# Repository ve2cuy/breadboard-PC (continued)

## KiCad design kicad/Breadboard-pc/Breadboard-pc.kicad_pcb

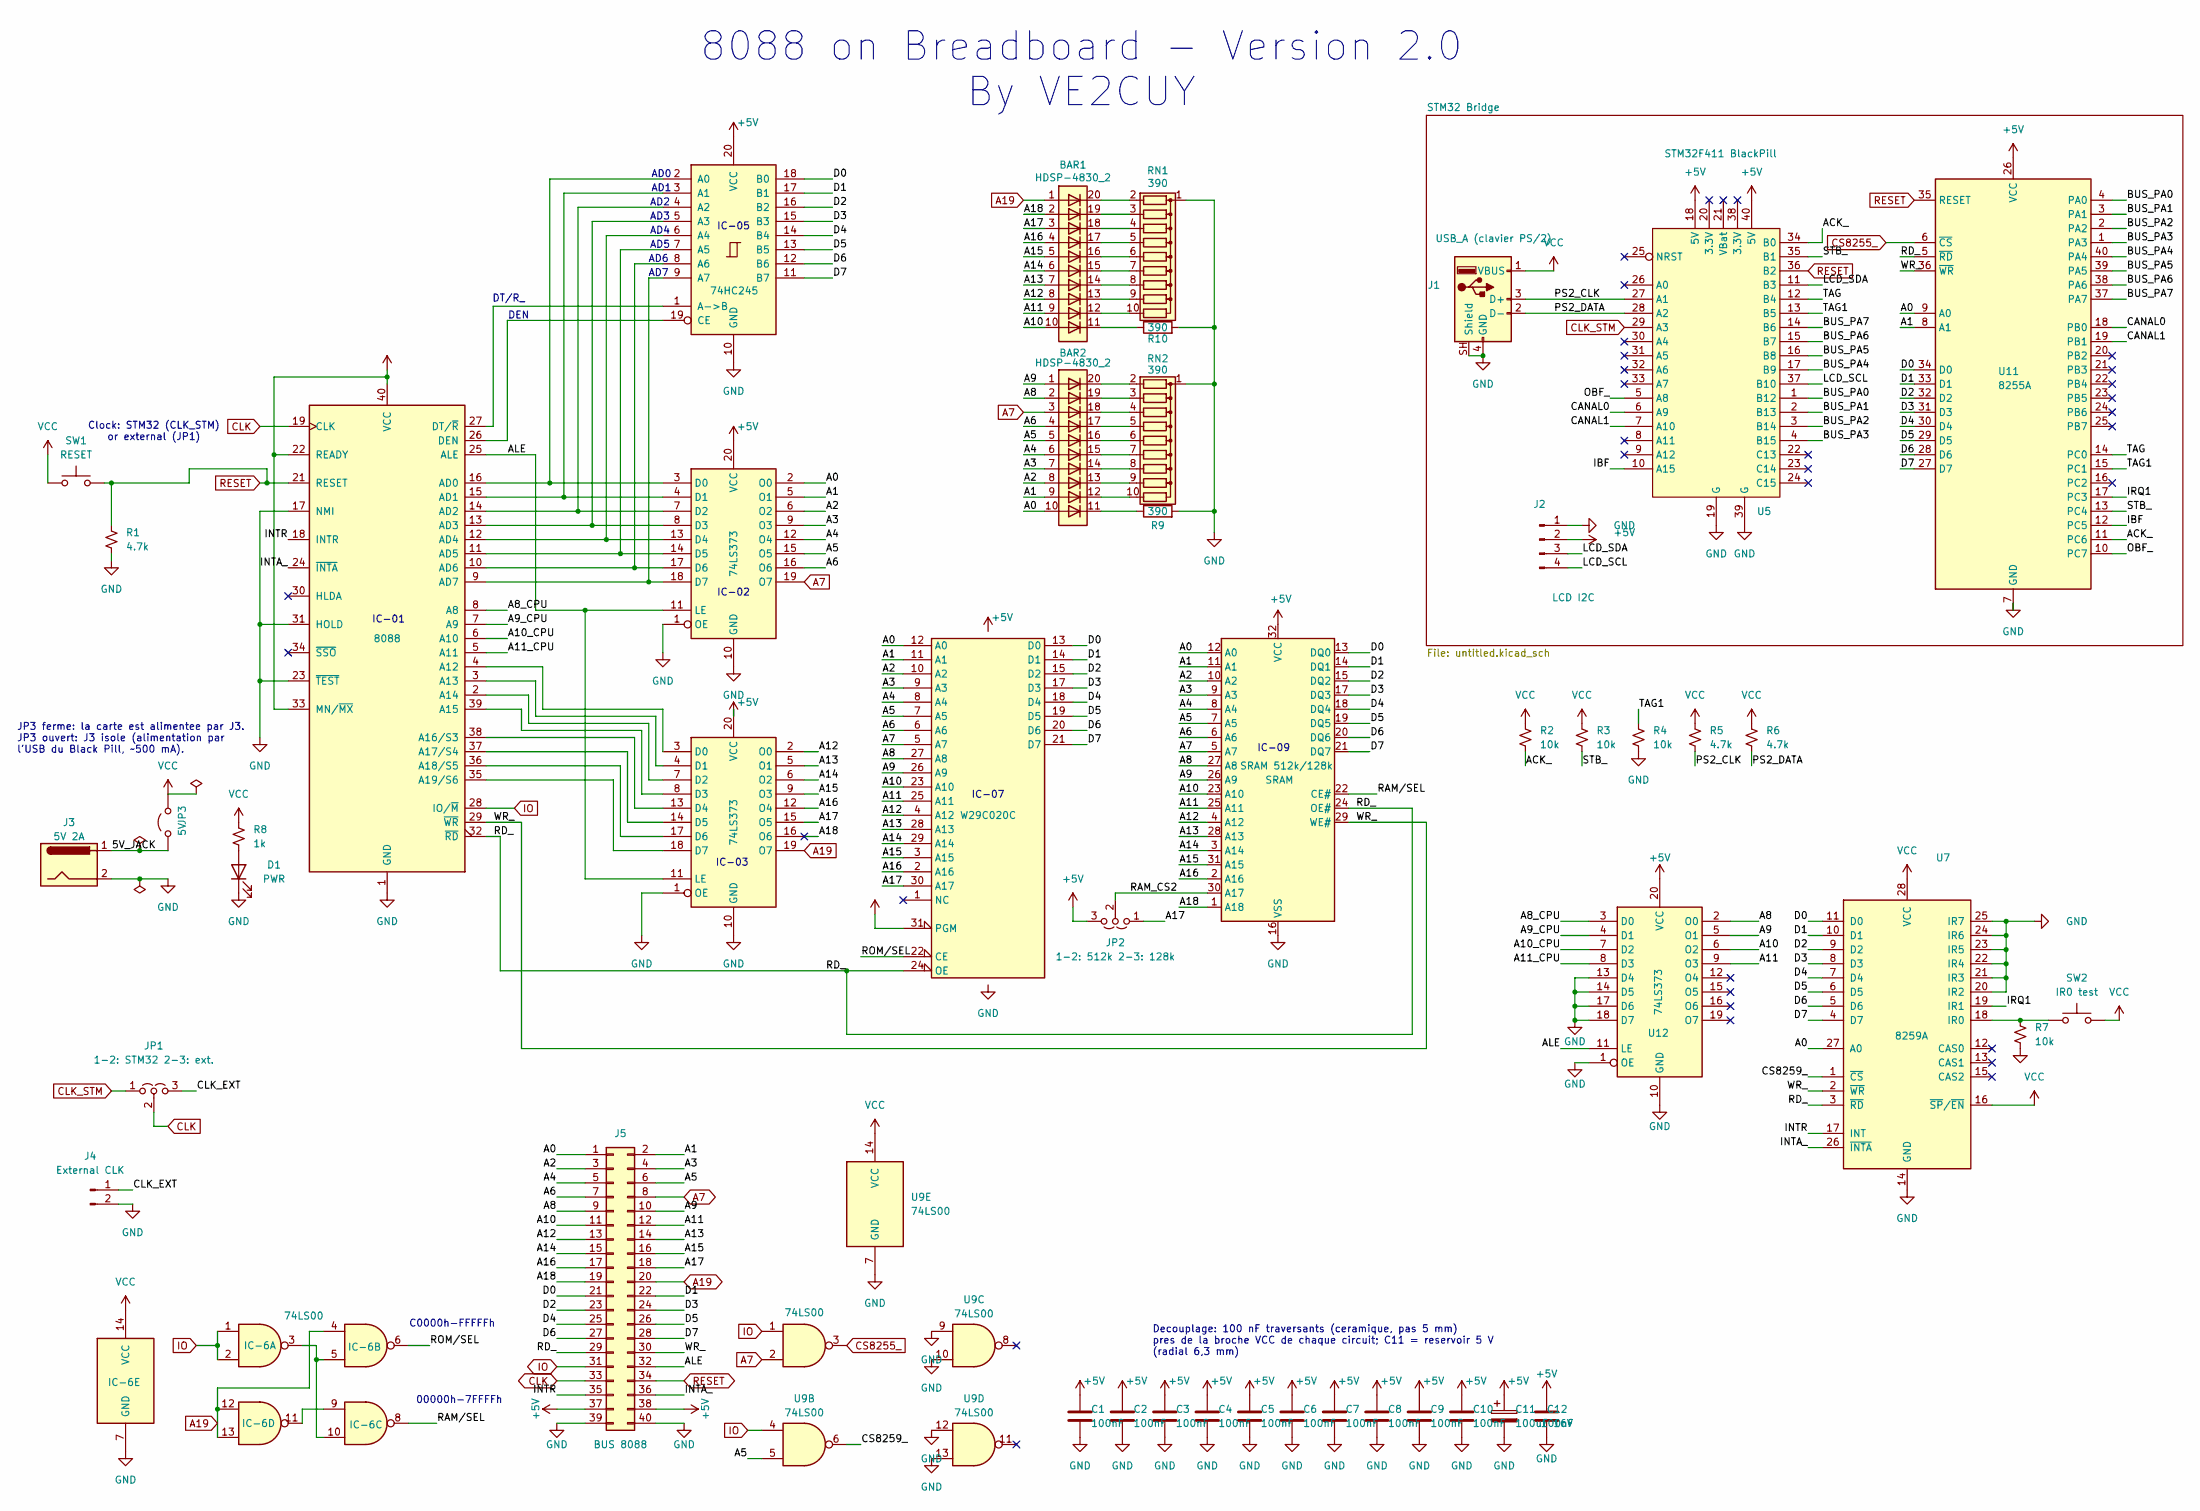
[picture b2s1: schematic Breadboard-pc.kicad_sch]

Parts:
BAR1, BAR2: HDSP-4830_2; HDSP-4830
C1, C2, C3, C4, C5, C6, C7, C8, C9, C10, C12: 100nF; C_Disc_D5.0mm_W2.5mm_P5.00mm
C11: 100uF 16V; CP_Radial_D6.3mm_P2.50mm
D1: PWR; LED_D3.0mm
IC-6: 74LS00; DIP-14_W7.62mm
J1: USB_A (clavier PS/2); USB_A_Molex_67643_Horizontal
J2: LCD I2C; PinHeader_1x04_P2.54mm_Vertical
J3: 5V 2A; BarrelJack_Horizontal
J4: External CLK; PinHeader_1x02_P2.54mm_Vertical
J5: BUS 8088; PinHeader_2x20_P2.54mm_Vertical
JP1: 1-2: STM32 2-3: ext.; PinHeader_1x03_P2.54mm_Vertical
JP2: 1-2: 512k 2-3: 128k; PinHeader_1x03_P2.54mm_Vertical
JP3: 5V; PinHeader_1x02_P2.54mm_Vertical
R1, R5, R6: 4.7k; R_Axial_DIN0207_L6.3mm_D2.5mm_P7.62mm_Horizontal
R2, R3, R4, R7: 10k; R_Axial_DIN0207_L6.3mm_D2.5mm_P7.62mm_Horizontal
R8: 1k; R_Axial_DIN0207_L6.3mm_D2.5mm_P7.62mm_Horizontal
R9, R10: 390; R_Axial_DIN0207_L6.3mm_D2.5mm_P7.62mm_Horizontal
RN1, RN2: 390; R_Array_SIP10
SW1: RESET; SW_PUSH_6mm
SW2: IR0 test; SW_PUSH_6mm
U1: 8088; DIP-40_W15.24mm
U2, U3, U12: 74LS373; DIP-20_W7.62mm
U4: W29C020C; DIP_Socket-32_W11.9mm_W12.7mm_W15.24mm_W17.78mm_W18.5mm_3M_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
U5: STM32F411 BlackPill; STM32F411_Black_Pill
U6: 74HC245; DIP-20_W7.62mm
U7: 8259A; DIP-28_W15.24mm
U8: SRAM; DIP-32_W15.24mm
U9: 74LS00; DIP-14_W7.62mm
U11: 8255A; DIP-40_W15.24mm

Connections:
/5V_JACK: J3.1, JP3.1 (A)
/A0: BAR2.10 (A), J5.1, U2.2 (O0), U4.12 (A0), U7.27 (A0), U8.12 (A0), U11.9 (A0)
/A1: BAR2.9 (A), J5.2, U2.5 (O1), U4.11 (A1), U8.11 (A1), U11.8 (A1)
/A2: BAR2.8 (A), J5.3, U2.6 (O2), U4.10 (A2), U8.10 (A2)
/A3: BAR2.7 (A), J5.4, U2.9 (O3), U4.9 (A3), U8.9 (A3)
/A4: BAR2.6 (A), J5.5, U2.12 (O4), U4.8 (A4), U8.8 (A4)
/A5: BAR2.5 (A), J5.6, U2.15 (O5), U4.7 (A5), U8.7 (A5), U9.5
/A6: BAR2.4 (A), J5.7, U2.16 (O6), U4.6 (A6), U8.6 (A6)
/A8: BAR2.2 (A), J5.9, U4.27 (A8), U8.27 (A8), U12.2 (O0)
/A8_CPU: U1.8 (A8), U12.3 (D0)
/A9: BAR2.1 (A), J5.10, U4.26 (A9), U8.26 (A9), U12.5 (O1)
/A9_CPU: U1.7 (A9), U12.4 (D1)
/A10: BAR1.10 (A), J5.11, U4.23 (A10), U8.23 (A10), U12.6 (O2)
/A10_CPU: U1.6 (A10), U12.7 (D2)
/A11: BAR1.9 (A), J5.12, U4.25 (A11), U8.25 (A11), U12.9 (O3)
/A11_CPU: U1.5 (A11), U12.8 (D3)
/A12: BAR1.8 (A), J5.13, U3.2 (O0), U4.4 (A12), U8.4 (A12)
/A13: BAR1.7 (A), J5.14, U3.5 (O1), U4.28 (A13), U8.28 (A13)
/A14: BAR1.6 (A), J5.15, U3.6 (O2), U4.29 (A14), U8.3 (A14)
/A15: BAR1.5 (A), J5.16, U3.9 (O3), U4.3 (A15), U8.31 (A15)
/A16: BAR1.4 (A), J5.17, U3.12 (O4), U4.2 (A16), U8.2 (A16)
/A17: BAR1.3 (A), J5.18, JP2.1 (A), U3.15 (O5), U4.30 (A17)
/A18: BAR1.2 (A), J5.19, U3.16 (O6), U8.1 (NC)
/ACK_: R2.2, U5.34 (B0), U11.11 (PC6)
/ALE: J5.32, U1.25 (ALE), U2.11 (LE), U3.11 (LE), U12.11 (LE)
/BUS_PA0: U5.1 (B12), U11.4 (PA0)
/BUS_PA1: U5.2 (B13), U11.3 (PA1)
/BUS_PA2: U5.3 (B14), U11.2 (PA2)
/BUS_PA3: U5.4 (B15), U11.1 (PA3)
/BUS_PA4: U5.17 (B9), U11.40 (PA4)
/BUS_PA5: U5.16 (B8), U11.39 (PA5)
/BUS_PA6: U5.15 (B7), U11.38 (PA6)
/BUS_PA7: U5.14 (B6), U11.37 (PA7)
/CANAL0: U5.6 (A9), U11.18 (PB0)
/CANAL1: U5.7 (A10), U11.19 (PB1)
/CLK_EXT: J4.1, JP1.3 (B)
/CS8259_: U7.1 (~CS), U9.6
/D0: J5.21, U4.13 (D0), U6.18 (B0), U7.11 (D0), U8.13 (DQ0), U11.34 (D0)
/D1: J5.22, U4.14 (D1), U6.17 (B1), U7.10 (D1), U8.14 (DQ1), U11.33 (D1)
/D2: J5.23, U4.15 (D2), U6.16 (B2), U7.9 (D2), U8.15 (DQ2), U11.32 (D2)
/D3: J5.24, U4.17 (D3), U6.15 (B3), U7.8 (D3), U8.17 (DQ3), U11.31 (D3)
/D4: J5.25, U4.18 (D4), U6.14 (B4), U7.7 (D4), U8.18 (DQ4), U11.30 (D4)
/D5: J5.26, U4.19 (D5), U6.13 (B5), U7.6 (D5), U8.19 (DQ5), U11.29 (D5)
/D6: J5.27, U4.20 (D6), U6.12 (B6), U7.5 (D6), U8.20 (DQ6), U11.28 (D6)
/D7: J5.28, U4.21 (D7), U6.11 (B7), U7.4 (D7), U8.21 (DQ7), U11.27 (D7)
/IBF: U5.10 (A15), U11.12 (PC5)
/INTA_: J5.36, U1.24 (~INTA), U7.26 (~INTA)
/INTR: J5.35, U1.18 (INTR), U7.17 (INT)
/IRQ1: U7.19 (IR1), U11.17 (PC3)
/LCD_SCL: J2.4, U5.37 (B10)
/LCD_SDA: J2.3, U5.11 (B3)
/OBF_: U5.5 (A8), U11.10 (PC7)
/PS2_CLK: J1.3 (D+), R5.2, U5.27 (A1)
/PS2_DATA: J1.2 (D-), R6.2, U5.28 (A2)
/RAM_CS2: JP2.2 (C), U8.30 (CS2)
/RAM/SEL: IC-6.8, U8.22 (CE#)
/RD_: J5.29, U1.32 (~RD), U4.24 (OE), U7.3 (~RD), U8.24 (OE#), U11.5 (~RD)
/ROM/SEL: IC-6.6, U4.22 (CE)
/STB_: R3.2, U5.35 (B1), U11.13 (PC4)
/TAG: U5.12 (B4), U11.14 (PC0)
/TAG1: R4.1, U5.13 (B5), U11.15 (PC1)
/WR_: J5.30, U1.29 (~WR), U7.2 (~WR), U8.29 (WE#), U11.36 (~WR)
A7: BAR2.3 (A), J5.8, U2.19 (O7), U4.5 (A7), U8.5 (A7), U9.2
A19: BAR1.1 (A), IC-6.4, IC-6.12, IC-6.13, J5.20, U3.19 (O7)
CLK: J5.33, JP1.2 (C), U1.19 (CLK)
CLK_STM: JP1.1 (A), U5.29 (A3)
CS8255_: U9.3, U11.6 (~CS)
GND: C1.2, C2.2, C3.2, C4.2, C5.2, C6.2, C7.2, C8.2, C9.2, C10.2, C11.2, C12.2, D1.1 (K), IC-6.7 (GND), J1.4 (GND), J1.SH (Shield), J2.1, J3.2, J4.2, J5.39, J5.40, R1.2, R4.2, R7.2, R9.2, R10.2, RN1.1 (common), RN2.1 (common), U1.1 (GND), U1.17 (NMI), U1.20 (GND), U1.23 (~TEST), U1.31 (HOLD), U2.1 (OE), U2.10 (GND), U3.1 (OE), U3.10 (GND), U4.16 (GND), U5.19 (G), U5.39 (G), U6.10 (GND), U7.14 (GND), U7.20 (IR2), U7.21 (IR3), U7.22 (IR4), U7.23 (IR5), U7.24 (IR6), U7.25 (IR7), U8.16 (VSS), U9.7 (GND), U9.9, U9.10, U9.12, U9.13, U11.7 (GND), U12.1 (OE), U12.10 (GND), U12.13 (D4), U12.14 (D5), U12.17 (D6), U12.18 (D7)
IO: IC-6.1, IC-6.2, J5.31, U1.28 (IO/~M), U9.1, U9.4
unnamed: BAR1.11 (K), R10.1
unnamed: BAR2.11 (K), R9.1
unnamed: D1.2 (A), R8.2
unnamed: IC-6.3, IC-6.5, IC-6.10
unnamed: IC-6.9, IC-6.11
unnamed: BAR1.20 (K), RN1.2 (R1)
unnamed: BAR1.19 (K), RN1.3 (R2)
unnamed: BAR1.18 (K), RN1.4 (R3)
unnamed: BAR1.17 (K), RN1.5 (R4)
unnamed: BAR1.16 (K), RN1.6 (R5)
unnamed: BAR1.15 (K), RN1.7 (R6)
unnamed: BAR1.14 (K), RN1.8 (R7)
unnamed: BAR1.13 (K), RN1.9 (R8)
unnamed: BAR1.12 (K), RN1.10 (R9)
unnamed: BAR2.20 (K), RN2.2 (R1)
unnamed: BAR2.19 (K), RN2.3 (R2)
unnamed: BAR2.18 (K), RN2.4 (R3)
unnamed: BAR2.17 (K), RN2.5 (R4)
unnamed: BAR2.16 (K), RN2.6 (R5)
unnamed: BAR2.15 (K), RN2.7 (R6)
unnamed: BAR2.14 (K), RN2.8 (R7)
unnamed: BAR2.13 (K), RN2.9 (R8)
unnamed: BAR2.12 (K), RN2.10 (R9)
unnamed: U1.4 (A12), U3.3 (D0)
unnamed: U1.3 (A13), U3.4 (D1)
unnamed: U1.2 (A14), U3.7 (D2)
unnamed: U1.39 (A15), U3.8 (D3)
unnamed: U1.38 (A16/S3), U3.13 (D4)
unnamed: U1.37 (A17/S4), U3.14 (D5)
unnamed: U1.36 (A18/S5), U3.17 (D6)
unnamed: U1.35 (A19/S6), U3.18 (D7)
unnamed: U1.16 (AD0), U2.3 (D0), U6.2 (A0)
unnamed: U1.15 (AD1), U2.4 (D1), U6.3 (A1)
unnamed: U1.14 (AD2), U2.7 (D2), U6.4 (A2)
unnamed: U1.13 (AD3), U2.8 (D3), U6.5 (A3)
unnamed: U1.12 (AD4), U2.13 (D4), U6.6 (A4)
unnamed: U1.11 (AD5), U2.14 (D5), U6.7 (A5)
unnamed: U1.10 (AD6), U2.17 (D6), U6.8 (A6)
unnamed: U1.9 (AD7), U2.18 (D7), U6.9 (A7)
unnamed: U1.26 (DEN), U6.19 (CE)
unnamed: U1.27 (DT/~R), U6.1 (A->B)
unnamed: R7.1, SW2.1, U7.18 (IR0)
RESET: J5.34, R1.1, SW1.2, U1.21 (RESET), U5.36 (B2), U11.35 (RESET)

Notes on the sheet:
IC-07
Decouplage: 100 nF traversants (ceramique, pas 5 mm) pres de la broche VCC de chaque circuit; C11 = reservoir 5 V (radial 6,3 mm)
C0000h-FFFFFh
00000h-7FFFFh
IC-05
AD2
DEN
IC-01
AD5
IC-03
AD4
AD0
DT/R_
IC-09
AD3
JP3 ferme: la carte est alimentee par J3. JP3 ouvert: J3 isole (alimentation par l'USB du Black Pill, ~500 mA).
IC-02
AD6
AD1
Clock: STM32 (CLK_STM) or external (JP1)
AD7
8088 on Breadboard - Version 2.0 By VE2CUY

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
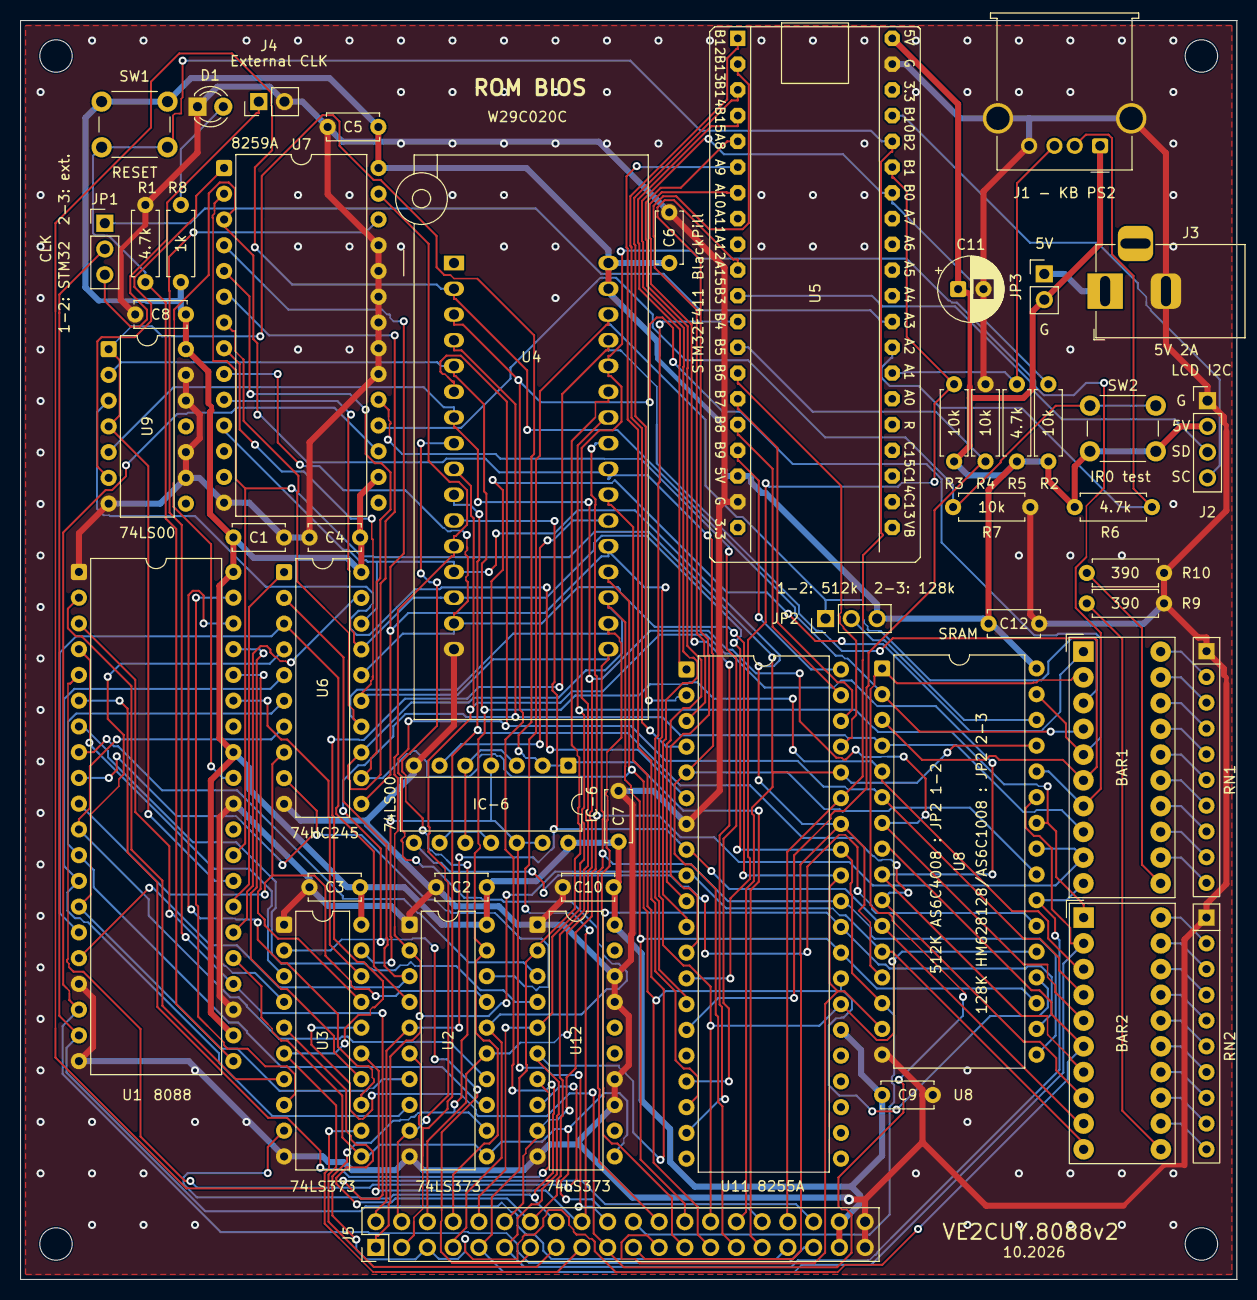
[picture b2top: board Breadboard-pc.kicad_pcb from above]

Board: 2 copper layers, 120.0 x 124.2 mm, 53 parts (0 on the bottom side), 113 nets.

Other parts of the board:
H1, H2, H3, H4: M3; MountingHole_3.2mm_M3

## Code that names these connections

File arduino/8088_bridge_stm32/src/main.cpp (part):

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//   - UART          : port serie virtuel USB (USB natif, "Serial") <-> 8088;
//   - LCD 20x4 I2C  : possede le bus I2C et le protocole PCF8574/HD44780.
//
// 8088 -> pont : le 8088 pose le CANAL sur le Port B (PB0/PB1 du 8255) puis
//     ecrit le Port A; OBF# passe a 0. On lit le canal, on abaisse ACK#, on lit
//     l'octet, on relache ACK#. canal 0 = octet UART, 1 = commande LCD, 2 =
//     donnee LCD.
// pont -> 8088 : on pose l'etiquette TAG (PC0: 0 = scan code, 1 = octet UART
//     recu; PC1 = 1: REPONSE a une commande), l'octet sur le bus, et on pulse
//     STB#; INTR du 8255 (sur IR1 du 8259) interrompt le 8088.
// canal 3 = COMMANDES pour le pont (voir Solution-01/lib/bridge.asm):
//     00h PING (reponse B1h, 3, capacites)   01h LIRE l'heure (reponse: 8 octets)
//     02h + 7 octets REGLER l'heure (annee 2 octets, mois, jour, h, min, s).
//     03h VERSION du firmware (PAS le "3" de PING ci-dessus, qui est le numero
//     de VERSION DU PROTOCOLE - sans rapport) -> 2 octets (majeure, mineure).
//     Necessite TAG1 (PB5) relie a PC1 du 8255 (tire a 0 par 10 kohm).
//     10h-19h = DISQUE: fichiers FAT (racine, noms 8.3) sur la flash SPI (W25Q64, 8 Mo) de la carte
//     (PA4 = CS, SPI1 PA5/PA6/PA7): statut, formater, ouvrir, lire, ecrire, fermer,
//     repertoire (debut / suivant), supprimer, espace libre. Voir lib/bridge.asm.
//     2Ch + 1 octet (action) = HORLOGE du 8088 (PA3, PWM materiel, voir clockExec ci-dessous):
//     0 lire, 1 +0,1 MHz, 2 -0,1 MHz, 3 +1 MHz, 4 -1 MHz, 5 -> 4,77 MHz, 6 -> 8 MHz
//     -> reponse 4 octets = Hz resultant.
//     Horloge de 1 Hz a 10 MHz (pont 2.0) par raccourcis traites ICI, sans le 8088 (a 1 Hz il
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//     l'appelle par INT 1Ah AH=E0h). Arret au reset du 8088.
//
// CABLAGE (voir le tableau du README.md)
//   D0-D3 <-> PB12-PB15 et D4-D7 <-> PB6-PB9  <->  8255 PA0-PA7 (bus de donnees)
//   PB0 -> ACK# (PC6)   PB1 -> STB# (PC4)   PA8 <- OBF# (PC7)   PB4 -> TAG (PC0)
//   PA9 <- canal bit 0 (8255 PB0)   PA10 <- canal bit 1 (8255 PB1)
//   PA15 <- IBF (PC5, facultatif)   PB5 -> TAG1 (PC1)
//   PA3 -> CLK du 8088 (broche 19, PWM materiel TIM2 CH4 - remplace le fil depuis l'Arduino UNO
//   R4 de projets/Clock-8088/; PA3 servait a TAG2/PC2, jamais cablee sur ce montage - libre)
//   PA1 <- CLK PS/2   PA2 <- DATA PS/2   PB10 = SCL, PB3 = SDA (LCD I2C2)
//   PA11/PA12 = USB, PA13/PA14 = SWD, PC13 = LED, PA4-PA7 = flash SPI (reservees),
//   PB2 -> RESET du 8088 (broche 21, actif HAUT; 4,7 kohm (R1) vers la masse sur le montage, bouton vers +5 V):
//   poussee HAUT pour un reset (demarrage du pont, Ctrl-Alt-Suppr au PS/2, Ctrl-\ au terminal), sinon
//   ENTREE (ne gene pas le bouton, jamais forcee BAS). PB2 = BOOT1: au repos la ligne est BASSE (4,7 kohm),
//   le mode DFU (BOOT0 = 1, BOOT1 = 0) reste donc utilisable.   PA0 = bouton K1 de la carte
// Selon la fiche technique du STM32F411 (DS10314 Rev 8, tableau 8), TOUTES ces
// broches sont tolerantes 5 V (FT) SAUF PA0 et PB5 (TC, 3,3 V): PB5 n'est donc
// utilisee qu'en SORTIE (TAG1). Ne jamais y relier une sortie 5 V.
// ============================================================================
#include <Wire.h>
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
// ---- reglages -------------------------------------------------------------
#define LCD_ADDR    0x27     // 0x3F pour un PCF8574A
// IBF (PC5 du 8255) cable sur PA15 ? 1 = oui: on n'envoie un octet que si le 8088 a lu le
// precedent (aucun octet ecrase); 0 = non cable. Non cable, PA15 est tiree a 0 (= libre).
#define USE_IBF     1
// Espace MINIMAL entre deux octets pont -> 8088, en plus de IBF. Le 8088 met ~ 0,5 ms
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#define ACK_BIT   0                  // GPIOB, sortie drain ouvert (10 kohm vers +5 V)
#define STB_BIT   1                  // GPIOB, sortie drain ouvert (10 kohm vers +5 V)
#define TAG_BIT   4                  // GPIOB, sortie
#define TAG1_BIT  5                  // GPIOB, sortie SEULEMENT (PB5 n'est pas tolerante 5 V)
#define OBF_BIT   8                  // GPIOA, entree
#define CH0_BIT   9                  // GPIOA, entrees (canal = Port B du 8255)
#define CH1_BIT   10
#define IBF_BIT   15                 // GPIOA, entree (facultatif)
#define PS2_CLK_BIT  1               // GPIOA, interruption EXTI1
#define PS2_DATA_BIT 2               // GPIOA
const uint32_t PIN_ACK = PB0, PIN_STB = PB1, PIN_TAG = PB4;
const uint32_t PIN_OBF = PA8, PIN_CH0 = PA9, PIN_CH1 = PA10, PIN_IBF = PA15;
const uint32_t PIN_TAG1 = PB5;                         // PC1 (etiquette etendue, futur)
const uint32_t PIN_PS2_CLK = PA1, PIN_PS2_DATA = PA2;
const uint32_t PIN_SCL = PB10, PIN_SDA = PB3;          // I2C2 (AF4 / AF9)
const uint32_t PIN_CLK8088 = PA3;                      // TIM2 CH4: horloge du 8088 (broche CLK, 19) -
                                                         // remplace le fil depuis l'Arduino UNO R4 (projets/Clock-8088)
                                                         // - PA3 servait a TAG2/PC2, jamais cablee sur ce montage

// Bus de donnees sur GPIOB, en deux quartets: D0-D3 = PB12-PB15, D4-D7 = PB6-PB9
#define BUS_ODR_MASK   ((0xFUL << 12) | (0xFUL << 6))
#define BUS_MODER_MASK 0xFF0FF000UL  // 2 bits par broche: PB12-15 (bits 24-31) et PB6-9 (bits 12-19)
#define BUS_MODER_OUT  0x55055000UL  // 01 = sortie
// Sur le montage, les broches PA4-PA7 du 8255 arrivent dans l'ORDRE INVERSE
// (constate: espace 0x20 recu 0x40, 'p' 0x70 recu 0xE0): le quartet haut est
// inverse (D4<->D7, D5<->D6), comme sur l'UNO. 1 = corrige en logiciel, 0 = bus
// cable dans l'ordre (D0-D7 <-> PA0-PA7).
#define BUS_HIGH_NIBBLE_REVERSED 1

// ---- canaux 8088 -> pont (Port B du 8255) ---------------------------------
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}

// ============================================================================
// Bus Port A du 8255 = PB12-PB15 (D0-D3) + PB6-PB9 (D4-D7) (MODER/BSRR/IDR)
// ============================================================================
static inline void busRelease() {          // haute impedance, sans pull
  GPIOB->MODER &= ~BUS_MODER_MASK;         // 00 = entree
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  stbHigh();                               // front montant: le 8255 verrouille
  delayMicroseconds(2);
#if DEBUG_FS
  dbgIbfAfter = (uint8_t)((GPIOA->IDR >> IBF_BIT) & 1);   // IBF doit valoir 1 (octet non lu)
#endif
  busRelease();
}
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}

// ============================================================================
// Horloge du 8088 (PA3 = TIM2 CH4, PWM materiel, duty cycle fixe 1/3 - voir
// projets/Clock-8088/src/main.cpp, meme principe mais sur l'Arduino UNO R4 separe
// d'origine: ici, l'horloge est generee par CE MEME pont, plus besoin de 2e carte).
// clockSetup() DOIT etre appelee EN PREMIER dans setup() (avant SPI/USB/RTC, qui
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
// ============================================================================
// Disque: systeme de fichiers FAT sur la flash SPI (W25Q64, 8 Mo) de la carte.
// Le STM32F411 n'a pas de QUADSPI: la flash s'utilise en SPI simple (SPI1: PA4 = CS,
// PA5 = SCK, PA6 = MISO, PA7 = MOSI). Fichiers a la racine, noms 8.3.
// ============================================================================
static Adafruit_FlashTransport_SPI flashTransport(PA4, SPI);
static Adafruit_SPIFlash flash(&flashTransport);
static FatVolume fatfs;
static bool flashOk = false, fsOk = false;
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}

// ============================================================================
// RESET materiel du 8088 (PB2 -> broche 21, RESET actif HAUT)
// Le montage tire RESET a la masse (4,7 kohm, R1) et son bouton le porte a +5 V: PB2 (tolerante 5 V) n'est
// donc JAMAIS forcee BAS - soit sortie HAUTE (reset en cours), soit ENTREE sans pull (le bouton marche).
// Demandes: demarrage du pont (setup: le 8088 reste en reset, horloge deja en marche, jusqu'a ce que le
// pont soit pret), Ctrl-Alt-Suppr au clavier PS/2 (kbdTrack, dans ps2Isr: detecte meme si le 8088 est
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#define RESET8088_BIT      2               // GPIOB
#define RESET8088_PULSE_MS 10UL            // >> 4 cycles d'horloge exiges par le 8088
#define RESET_UART_KEY     0x1C            // Ctrl-\ (terminal)
#define STUCK_MS           500UL           // IBF = 1 depuis ce delai: le 8088 ne lit plus (fige)
static volatile bool resetRequest = false;

static void reset8088Hold() {              // sortie HAUTE (ODR avant MODER: aucune impulsion basse)
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  // ACK#/STB#: DRAIN OUVERT. Le niveau haut est fourni par les 10 kohm vers +5 V
  // (vrai niveau 5 V pour le 8255, et lignes tenues hautes pendant un reset du
  // STM32). Pull-up interne en secours (3,3 V, suffisant pour l'entree TTL du 8255).
  pinMode(PIN_ACK, OUTPUT_OPEN_DRAIN);  ackHigh();  pullUp(GPIOB, ACK_BIT);
  pinMode(PIN_STB, OUTPUT_OPEN_DRAIN);  stbHigh();  pullUp(GPIOB, STB_BIT);
  pinMode(PIN_TAG, OUTPUT);   digitalWrite(PIN_TAG, LOW);
  pinMode(PIN_TAG1, OUTPUT);  digitalWrite(PIN_TAG1, LOW);   // PC1 (inutilise pour l'instant)
  pinMode(PIN_OBF, INPUT_PULLUP);          // 8255 absent/hors tension = "rien"
  pinMode(PIN_CH0, INPUT);
  pinMode(PIN_CH1, INPUT);
  pinMode(PIN_IBF, INPUT_PULLDOWN);        // non cable = "libre"

  // Bus (PB6-PB9, PB12-PB15): entrees, sans pull, sorties push-pull rapides.
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
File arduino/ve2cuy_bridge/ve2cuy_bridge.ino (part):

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// Le 8088 ne voit qu'UN bus de 8 bits: le Port A du 8255 en MODE 2, avec la
// poignee de main materielle du 8255 (voir Directives.md, hardware.inc):
//
//   8088 -> Arduino : le 8088 pose le CANAL sur le Port B (PB0/PB1) puis ecrit
//       le Port A; OBF# (PC7) passe a 0. On lit le canal, on abaisse ACK#
//       (PC6): le 8255 pilote alors le bus, on lit l'octet, on relache ACK#.
//       canal 0 = octet UART a emettre, 1 = commande LCD, 2 = donnee LCD.
//   Arduino -> 8088 : on pose l'etiquette (PC0: 0 = scan code, 1 = octet UART
//       recu), on pose l'octet sur le bus et on pulse STB# (PC4); INTR du 8255
//       (cable sur IR1 du 8259) interrompt le 8088.
//
// CABLAGE (18 broches, aucun circuit integre supplementaire)
//   D2  <- CLK  clavier PS/2 (interruption INT0)
//   D3  <- DATA clavier PS/2
//   D4  -> ACK#  8255 PC6        (repos: HAUT)   + pull-up 10k vers +5V conseille
//   D5  -> STB#  8255 PC4        (repos: HAUT)   + pull-up 10k vers +5V conseille
//   D6  <- OBF#  8255 PC7
//   D7  -> TAG   8255 PC0
//   D8  <- CH0   8255 PB0
//   D9  <- CH1   8255 PB1
//   D10 D11 D12 D13 A3 A2 A1 A0  <->  8255 PA0 PA1 PA2 PA3 PA4 PA5 PA6 PA7
//   (soit D10-D13 = PA0-PA3, A3=PA4, A2=PA5, A1=PA6, A0=PA7 - voir BUS[])
//   A4 (SDA), A5 (SCL) -> module LCD I2C (PCF8574, adresse 0x27 ou 0x3F)
//   INTR du 8255 (PC3) -> IR1 du 8259 (plus aucune sortie IR sur l'Arduino)
//   D0/D1 : reserves a l'USB (UART vers le PC) - ne rien y brancher.
//   Masse commune Arduino / breadboard 8088.
//
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#define DEBUG_PS2   0        // 1 = trace PS/2 sur le terminal (Serial), voir dbg*()

// ---- broches --------------------------------------------------------------
const uint8_t PIN_PS2_CLK  = 2;   // = PD2 (INT0) - ps2Isr lit PIND directement: garder CLK/DATA sur PD0-PD7
const uint8_t PIN_PS2_DATA = 3;
const uint8_t PIN_ACK      = 4;
const uint8_t PIN_STB      = 5;
const uint8_t PIN_OBF      = 6;
const uint8_t PIN_TAG      = 7;
const uint8_t PIN_CH0      = 8;
const uint8_t PIN_CH1      = 9;
// Ordre selon le CABLAGE REEL constate sur le montage: A0..A3 sont relies a
// PA7..PA4 (ordre inverse - les broches du 8255 sont numerotees 4,3,2,1 puis
// 40,39,38,37 pour PA0..PA7). Si vous recablez A3->PA7 ... A0->PA4, remettez
// {10, 11, 12, 13, A0, A1, A2, A3}.
const uint8_t BUS[8]       = {10, 11, 12, 13, A3, A2, A1, A0};

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
// Arduino -> 8088: octet + etiquette, puis impulsion STB#.
static void sendTo8088(uint8_t tag, uint8_t v) {
  digitalWrite(PIN_TAG, tag);
  for (uint8_t i = 0; i < 8; i++) {
    digitalWrite(BUS[i], (v >> i) & 1);    // niveau AVANT de passer en sortie
    pinMode(BUS[i], OUTPUT);
  }
  delayMicroseconds(2);
  digitalWrite(PIN_STB, LOW);
  delayMicroseconds(2);
  digitalWrite(PIN_STB, HIGH);             // front montant: le 8255 verrouille
  delayMicroseconds(2);
  busRelease();
}
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// pilote le bus; les broches sont des entrees a ce moment-la. Le canal (Port
// B) est stable depuis que le 8088 a ecrit le Port A - meme instantane.
static bool takeFrom8088(uint8_t &chan, uint8_t &val) {
  if (digitalRead(PIN_OBF)) return false;  // rien en attente
  digitalWrite(PIN_ACK, LOW);
  delayMicroseconds(2);                    // tAOD du 8255 < 200 ns
  uint32_t s = snapPorts();
  digitalWrite(PIN_ACK, HIGH);
  chan = (uint8_t)(snapBit(s, PIN_CH0) | (snapBit(s, PIN_CH1) << 1));
  val = 0;
  for (uint8_t i = 0; i < 8; i++) val |= (uint8_t)(snapBit(s, BUS[i]) << i);
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  uint32_t now = micros();
  ps2Act = now;
  delayMicroseconds(PS2_GLITCH_US);
  if (PIND & _BV(PIN_PS2_CLK)) { dbg(0x700); return; }   // CLK repassee haute: parasite

  // DATA: vote majoritaire sur 3 lectures (encore stable a ce stade du cycle)
  uint8_t votes = 0;
  if (PIND & _BV(PIN_PS2_DATA)) votes++;
  delayMicroseconds(2);
  if (PIND & _BV(PIN_PS2_DATA)) votes++;
  delayMicroseconds(2);
  if (PIND & _BV(PIN_PS2_DATA)) votes++;
  uint8_t b = (votes >= 2) ? 1 : 0;

  if ((uint32_t)(now - ps2Last) > PS2_FRAME_GAP_US) {   // nouvelle trame
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
// ============================================================================
void setup() {
  pinMode(PIN_ACK, OUTPUT);  digitalWrite(PIN_ACK, HIGH);
  pinMode(PIN_STB, OUTPUT);  digitalWrite(PIN_STB, HIGH);
  pinMode(PIN_TAG, OUTPUT);  digitalWrite(PIN_TAG, LOW);
  pinMode(PIN_OBF, INPUT_PULLUP);          // 8255 absent/hors tension = "rien"
  pinMode(PIN_CH0, INPUT);
  pinMode(PIN_CH1, INPUT);
  busRelease();
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#endif
  lcdInit();

  pinMode(PIN_PS2_CLK, INPUT_PULLUP);
  pinMode(PIN_PS2_DATA, INPUT_PULLUP);
  attachInterrupt(digitalPinToInterrupt(PIN_PS2_CLK), ps2Isr, FALLING);
}

void loop() {
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
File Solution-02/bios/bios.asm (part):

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;        Sans 8259 (detecte au menu par relecture du masque) : scrutation comme le 0.7.
;        IRQ0 (INT 08h) = OUT0 de la 8253 : temps (BDA, INT 1Ch) et LED Show en arriere-plan.
;   O3 : 30h-33h = 2e 8255 (U12) : mot 82h (PA, PC en sortie, PB en entree).
;        Clavier PS/2 (J4, prise USB-A) : PB0 = horloge, PB1 = donnees.
;        UART logiciel 9600 8N1 (J5) : PA7 = TX, PB2 = RX.
;   O4 : 40h-43h = 8253 (U15, NEC D8253C-2) : CLK0-2 = PCLK (2,67 MHz), compteur 0 en mode 3, diviseur
;        PIT_DIV = 36617 -> IRQ0 a 72,83 Hz = 4 x 18,2065 Hz (un top du PC sur 4).
;        Detecte au demarrage (deux lectures verrouillees qui different et <= PIT_DIV).
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;      RAM bonne : effacement a 0, PILE en DSEG:1000h verifiee par PUSH/POP,
;      "PILE OK  Touche=menu" ; RAM defectueuse : pas de pile, "RAM DEFAUT  CPT nnnn".
;   LED Show : 9 animations en boucle sur les 24 DEL du 8255, disposees de gauche a
;      droite PC7..PC0, PA7..PA0, PB7..PB0 ; ligne 2 = nom de l'animation + nombre
;      de cycles. Pendant les attentes, scrutation du clavier PS/2 et de l'UART :
;      touche -> LCD ligne 3 + UART ; octet recu de l'UART -> LCD ligne 4 + echo.
;
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PPI_MODE0_SORTIES equ   80h             ; mode 0, PA, PB et PC en sortie

; 2e 8255 (U12) sur O3 du 74LS138 : clavier PS/2 et UART logiciel (bit-bang)
PPI2_PA         equ     30h             ; PA7 = UART TX (sortie)
PPI2_PB         equ     31h             ; PB0 = horloge clavier, PB1 = donnees, PB2 = UART RX
PPI2_PC         equ     32h
PPI2_CTRL       equ     33h
PPI2_MODE       equ     82h             ; mode 0 : PA et PC en sortie, PB en entree
KBD_CLK         equ     01h             ; PB0
KBD_DATA        equ     02h             ; PB1
UART_RX         equ     04h             ; PB2
UART_TX         equ     80h             ; PA7
; Blocage du clavier (comme le PC/AT) : diode Schottky de KBD_CLK (anode) vers PC0 de
; U12 (cathode). PC0 = 0 tient l'horloge basse : le clavier garde ses touches et
; interrompt (puis renvoie) une trame commencee. Commande par mise a 0/1 d'un bit
; (BSR) : PA7 (TX) n'est pas touche. Sans la diode, sans effet.
KBD_BLOQUE      equ     00h             ; BSR : PC0 = 0
KBD_LIBRE       equ     01h             ; BSR : PC0 = 1

; UART 9600 8N1 : iterations de LOOP par bit, A CALIBRER a l'oscilloscope (bit = 104,2 us).
; Estimation pour un 8088 a 5,33 MHz : ~70 cycles fixes + 17 par iteration = 555 cycles.
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; ---- 2e 8255 (U12) en premier : TX de l'UART au repos (1) le plus tot possible ----
        mov     al, PPI2_MODE           ; PA et PC en sortie, PB en entree
        out     PPI2_CTRL, al
                                        ; (le mot de mode met PC0 a 0 : clavier bloque
                                        ;  tant que le BIOS ne l'ecoute pas)
        mov     al, UART_TX             ; PA7 = 1 (repos)
        out     PPI2_PA, al
        mov     al, AVR_REPOS           ; PC0 = 1 (ATmega libre), CS de la carte SD = 1
        out     PPI2_PC, al             ; (le mot de mode les avait mis a 0)

; ---- 8259A (U13) : initialise, tout masque (sans effet s'il est absent) ----------
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
%ifdef DIAG_U12
; ---- ROM de diagnostic du 2e 8255 U12 (make diag2) ------------------------------
; PC et PA de U12 clignotent (55h <-> AAh, ~0,3 s ; PC0 reste a 1) ; le mot de controle 82h est
; renvoye a chaque inversion. Ligne 3 : PB lu en direct (CLK = PB0, DATA = PB1).
; Ligne 4 : dernier octet PS/2 recu, nombre de trames bonnes / en erreur (hexa).
; La RAM ayant ete validee, la pile est mise en 7000:0000 sans test (pour ps2_trame).
        mov     ax, 7000h
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        out     PPI2_CTRL, al
        mov     al, bl
        out     PPI2_PA, al
        or      al, KBD_LIBRE           ; PC0 = 1 : clavier libre (diode de blocage)
        out     PPI2_PC, al
        LCD_COMMANDE (80h | LIGNE2 + 3) ; "PC=55 PA=55"
        LCD_HEX8 bl
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
; =============================================================================
; Animations des 24 DEL. Disposition du montage, de gauche a droite :
;   PC7 ... PC0   PA7 ... PA0   PB7 ... PB0
; Rangee logique de 24 bits DL:BH:BL, bit 23 = DEL la plus a GAUCHE (PC7), bit 0 =
; DEL la plus a DROITE (PB0) : DL = PC, BH = PA, BL = PB. Decaler vers la droite =
; SHR DL / RCR BH / RCR BL.
; DI = duree d'un pas, en IRQ0 (13,7 ms). Chaque animation peut detruire AX, BX, CX, DX,
; SI, DI, BP.
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        jmp     .suite

; =============================================================================
; UART logiciel 9600 8N1 sur le 2e 8255 (U12) : TX = PA7, RX = PB2 (tirage R4).
; Duree d'un bit = 7 + 17 x UART_N cycles environ par tour de boucle (voir
; uart_tx) : a regler a l'oscilloscope (bit = 104,2 us a 9600 bauds ; 1 unite de
; UART_N = 17 cycles = 3,2 us a 5,33 MHz). Interruptions masquees pendant l'octet.
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        in      al, PPI2_PB
        shr     al, 1
        shr     al, 1
        shr     al, 1                   ; CF = PB2
        rcr     ah, 1
        dec     bl
        jnz     .bit
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        ret

; =============================================================================
; Clavier PS/2 (bit-bang, comme Solution-01) sur le 2e 8255 : PB0 = horloge,
; PB1 = donnees (tirages R2/R3). Le clavier fournit l'horloge (10-16,7 kHz) ;
; une donnee est valide pendant que l'horloge est basse. Trame : depart (0),
; 8 donnees (bit 0 d'abord), parite impaire, arret (1).
; =============================================================================
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        mov     bl, 11
.bit:   in      al, PPI2_PB             ; CLK bas : echantillonne DATA
        shr     al, 1
        shr     al, 1                   ; CF = PB1 (DATA)
        rcr     dx, 1
        dec     bl
        jz      .fin
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        pop     dx
        ret

; bit24 : allume la DEL numero CL (0 = PB0 a droite ... 23 = PC7 a gauche). Detruit AL, CL.
bit24:
        mov     al, 1
        cmp     cl, 8
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        mov     di, VIT_RAPIDE
        mov     ah, 2
.tour:  xor     bx, bx
        mov     dl, 80h                 ; PC7, a gauche
        mov     si, 24
.pas:   call    del_aff
        shr     dl, 1
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        mov     di, VIT_RAPIDE
        mov     ah, 3
.tour:  xor     bx, bx
        mov     dl, 0E0h                ; PC7-PC5, a gauche
        mov     si, 21
.aller: call    del_aff
        shr     dl, 1
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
